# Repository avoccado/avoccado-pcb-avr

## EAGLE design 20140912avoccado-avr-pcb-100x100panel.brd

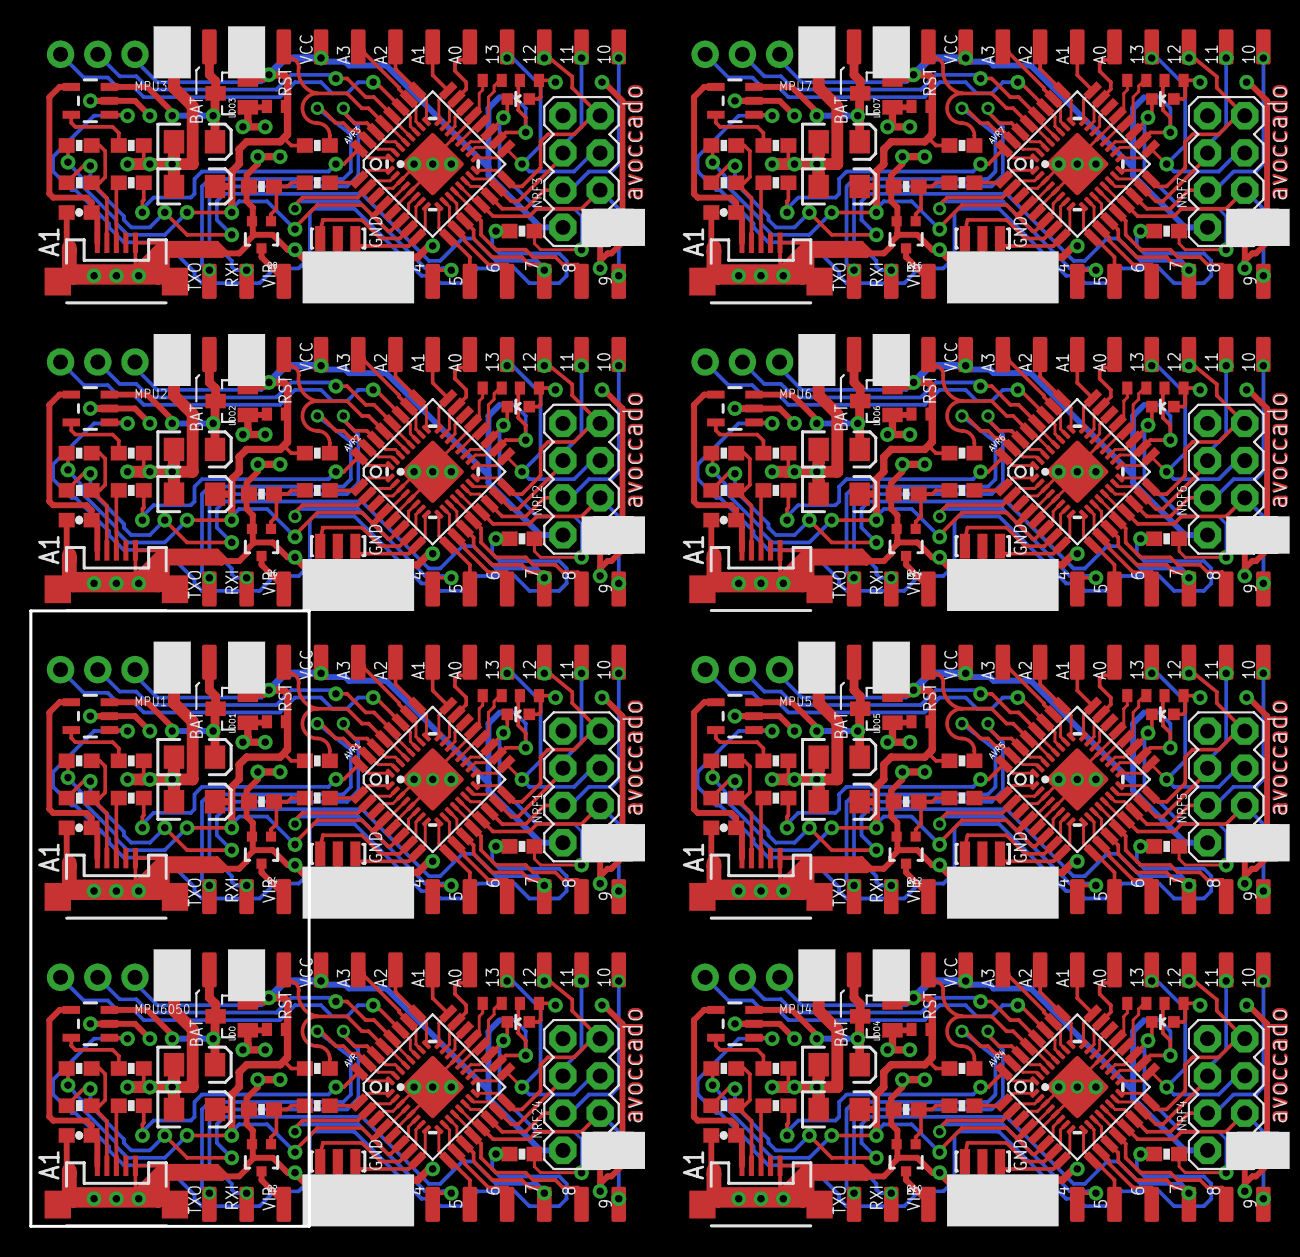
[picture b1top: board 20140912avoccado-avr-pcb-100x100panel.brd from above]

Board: 2 copper layers, 240 parts (0 on the bottom side), 288 nets.

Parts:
AVR, AVR1, AVR2, AVR3, AVR4, AVR5, AVR6, AVR7: ATMEGA328P; TQFP32-08
C1, C2, C3, C6, C7, C10, C11, C14, C15, C18, C21, C22, C25, C27, C28, C31, C33, C34, C37, C39, C40, C43, C45, C46: 0.1uF; C0402
C4, C9, C17, C24, C30, C36, C42, C48: 4.7uF; 0603-CAP
C5, C8, C12, C13, C16, C19, C20, C23, C26, C29, C32, C35, C38, C41, C44, C47: 10uF; EIA3216
D1, D2, D3, D4, D5, D6, D7, D8: LED; LED-0603
IC1, IC2, IC3, IC4, IC5, IC6, IC7, IC8: ATMEGA328P-20MU; MLF32
JP1, JP2, JP3, JP4, JP5, JP6, JP7, JP8, JP9, JP10, JP11, JP12, JP13, JP14, JP15, JP16, JP17, JP18, JP19, JP20, JP21, JP22, JP23, JP24, JP25, JP26, JP27, JP28, JP29, JP30, JP31, JP32, JP33, JP34, JP35, JP36, JP37, JP38, JP39, JP40, JP41, JP42, JP43, JP44, JP45, JP46, JP47, JP48: 1X04-SMD
LDO, LDO1, LDO2, LDO3, LDO4, LDO5, LDO6, LDO7: MCP1703CB; SOT23
MPU1, MPU2, MPU3, MPU4, MPU5, MPU6, MPU7, MPU6050: 1X04_NO_SILK
NRF1, NRF2, NRF3, NRF4, NRF5, NRF6, NRF7, NRF24: M04X2; 2X4
Q1, Q3, Q5, Q7, Q9, Q11, Q13, Q15: 16MHz; RESONATOR-SMD
Q2, Q4, Q6, Q8, Q10, Q12, Q14, Q16: FET; SOT323
R1, R10, R18, R26, R34, R42, R50, R58: 1K; 0603-RES
R2, R9, R17, R25, R33, R41, R49, R57: 10K; 0603-RES
R3, R4, R8, R11, R12, R16, R19, R20, R24, R27, R28, R32, R35, R36, R40, R43, R44, R48, R51, R52, R56, R59, R60, R64: 2K; 0603-RES
R5, R13, R21, R29, R37, R45, R53, R61: 1M; 0603-RES
R6, R7, R14, R15, R22, R23, R30, R31, R38, R39, R46, R47, R54, R55, R62, R63: 68; 0603-RES
U1, U2, U3, U4, U5, U6, U7, U8: MCP73831; SOT23-5
X1, X2, X3, X4, X5, X6, X7, X8: Micro USB; USB-MICROB

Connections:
3V1: AVR1.4, AVR1.6, AVR1.18, C2.1, C5.A, C6.2, IC1.4, IC1.6, IC1.18, JP1.4, LDO1.2, MPU1.2, NRF1.2, R9.2, R16.2
3V2: AVR2.4, AVR2.6, AVR2.18, C11.1, C12.A, C14.2, IC2.4, IC2.6, IC2.18, JP13.4, LDO2.2, MPU2.2, NRF2.2, R17.2, R24.2
3V3: AVR.4, AVR.6, AVR.18, C3.2, C10.1, C13.A, IC5.4, IC5.6, IC5.18, JP3.4, LDO.2, MPU6050.2, NRF24.2, R2.2, R8.2
3V4: AVR3.4, AVR3.6, AVR3.18, C18.1, C20.A, C21.2, IC3.4, IC3.6, IC3.18, JP19.4, LDO3.2, MPU3.2, NRF3.2, R25.2, R32.2
3V5: AVR4.4, AVR4.6, AVR4.18, C25.1, C26.A, C27.2, IC4.4, IC4.6, IC4.18, JP25.4, LDO4.2, MPU4.2, NRF4.2, R33.2, R40.2
3V6: AVR5.4, AVR5.6, AVR5.18, C31.1, C32.A, C33.2, IC6.4, IC6.6, IC6.18, JP31.4, LDO5.2, MPU5.2, NRF5.2, R41.2, R48.2
3V7: AVR6.4, AVR6.6, AVR6.18, C37.1, C38.A, C39.2, IC7.4, IC7.6, IC7.18, JP37.4, LDO6.2, MPU6.2, NRF6.2, R49.2, R56.2
3V8: AVR7.4, AVR7.6, AVR7.18, C43.1, C44.A, C45.2, IC8.4, IC8.6, IC8.18, JP43.4, LDO7.2, MPU7.2, NRF7.2, R57.2, R64.2
A0: AVR.23, IC5.23, JP5.4
A1: AVR.24, IC5.24, JP5.3
A2: AVR.25, IC5.25, JP5.2
A3: AVR.26, IC5.26, JP5.1
A4: AVR.27, IC5.27, MPU6050.4
A5: AVR.28, IC5.28, MPU6050.3
A6: AVR.19, D1.C, IC5.19, R4.1
A7: AVR.22, IC5.22
A8: AVR1.28, IC1.28, MPU1.3
A9: AVR1.27, IC1.27, MPU1.4
A10: AVR1.26, IC1.26, JP2.1
A11: AVR1.25, IC1.25, JP2.2
A12: AVR1.24, IC1.24, JP2.3
A13: AVR1.23, IC1.23, JP2.4
A14: AVR1.19, D2.C, IC1.19, R12.1
A15: AVR1.22, IC1.22
A16: AVR2.28, IC2.28, MPU2.3
A17: AVR2.27, IC2.27, MPU2.4
A18: AVR2.26, IC2.26, JP14.1
A19: AVR2.25, IC2.25, JP14.2
A20: AVR2.24, IC2.24, JP14.3
A21: AVR2.23, IC2.23, JP14.4
A22: AVR2.19, D3.C, IC2.19, R20.1
A23: AVR2.22, IC2.22
A24: AVR3.28, IC3.28, MPU3.3
A25: AVR3.27, IC3.27, MPU3.4
A26: AVR3.26, IC3.26, JP20.1
A27: AVR3.25, IC3.25, JP20.2
A28: AVR3.24, IC3.24, JP20.3
A29: AVR3.23, IC3.23, JP20.4
A30: AVR3.19, D4.C, IC3.19, R28.1
A31: AVR3.22, IC3.22
A32: AVR4.28, IC4.28, MPU4.3
A33: AVR4.27, IC4.27, MPU4.4
A34: AVR4.26, IC4.26, JP26.1
A35: AVR4.25, IC4.25, JP26.2
A36: AVR4.24, IC4.24, JP26.3
A37: AVR4.23, IC4.23, JP26.4
A38: AVR4.19, D5.C, IC4.19, R36.1
A39: AVR4.22, IC4.22
A40: AVR5.28, IC6.28, MPU5.3
A41: AVR5.27, IC6.27, MPU5.4
A42: AVR5.26, IC6.26, JP32.1
A43: AVR5.25, IC6.25, JP32.2
A44: AVR5.24, IC6.24, JP32.3
A45: AVR5.23, IC6.23, JP32.4
A46: AVR5.19, D6.C, IC6.19, R44.1
A47: AVR5.22, IC6.22
A48: AVR6.28, IC7.28, MPU6.3
A49: AVR6.27, IC7.27, MPU6.4
A50: AVR6.26, IC7.26, JP38.1
A51: AVR6.25, IC7.25, JP38.2
A52: AVR6.24, IC7.24, JP38.3
A53: AVR6.23, IC7.23, JP38.4
A54: AVR6.19, D7.C, IC7.19, R52.1
A55: AVR6.22, IC7.22
A56: AVR7.28, IC8.28, MPU7.3
A57: AVR7.27, IC8.27, MPU7.4
A58: AVR7.26, IC8.26, JP44.1
A59: AVR7.25, IC8.25, JP44.2
A60: AVR7.24, IC8.24, JP44.3
A61: AVR7.23, IC8.23, JP44.4
A62: AVR7.19, D8.C, IC8.19, R60.1
A63: AVR7.22, IC8.22
AREF: AVR.20, C1.2, IC5.20
AREF1: AVR1.20, C7.2, IC1.20
AREF2: AVR2.20, C15.2, IC2.20
AREF3: AVR3.20, C22.2, IC3.20
AREF4: AVR4.20, C28.2, IC4.20
AREF5: AVR5.20, C34.2, IC6.20
AREF6: AVR6.20, C40.2, IC7.20
AREF7: AVR7.20, C46.2, IC8.20
BUS: C4.1, U2.4, X1.VBUS
BUS1: C9.1, U1.4, X2.VBUS
BUS2: C17.1, U3.4, X3.VBUS
BUS3: C24.1, U4.4, X4.VBUS
BUS4: C30.1, U5.4, X5.VBUS
BUS5: C36.1, U6.4, X6.VBUS
BUS6: C42.1, U7.4, X7.VBUS
BUS7: C48.1, U8.4, X8.VBUS
D1: AVR1.13, IC1.13, JP6.1, NRF1.3
D2: AVR.32, IC5.32, R7.2
D3: AVR.1, IC5.1, R1.1
D4: AVR.2, IC5.2, JP10.2
D5: AVR.9, IC5.9, JP10.1
D6: AVR.10, IC5.10, JP9.4
D7: AVR.11, IC5.11, JP9.3, R6.2
D8: AVR.12, IC5.12, JP9.2
D9: AVR.13, IC5.13, JP9.1, NRF24.3
D10: AVR.14, IC5.14, JP8.4, NRF24.4
D11: AVR1.12, IC1.12, JP6.2
D12: AVR1.32, IC1.32, R15.2
D13: AVR1.1, IC1.1, R10.1
D14: AVR1.2, IC1.2, JP7.2
D15: AVR1.9, IC1.9, JP7.1
D16: AVR1.10, IC1.10, JP6.4
D17: AVR1.11, IC1.11, JP6.3, R14.2
D18: AVR1.14, IC1.14, JP4.4, NRF1.4
D19: AVR2.13, IC2.13, JP16.1, NRF2.3
D20: AVR2.12, IC2.12, JP16.2
D21: AVR2.32, IC2.32, R23.2
D22: AVR2.1, IC2.1, R18.1
D23: AVR2.2, IC2.2, JP17.2
D24: AVR2.9, IC2.9, JP17.1
D25: AVR2.10, IC2.10, JP16.4
D26: AVR2.11, IC2.11, JP16.3, R22.2
D27: AVR2.14, IC2.14, JP15.4, NRF2.4
D28: AVR3.13, IC3.13, JP22.1, NRF3.3
D29: AVR3.12, IC3.12, JP22.2
D30: AVR3.32, IC3.32, R31.2
D31: AVR3.1, IC3.1, R26.1
D32: AVR3.2, IC3.2, JP23.2
D33: AVR3.9, IC3.9, JP23.1
D34: AVR3.10, IC3.10, JP22.4
D35: AVR3.11, IC3.11, JP22.3, R30.2
D36: AVR3.14, IC3.14, JP21.4, NRF3.4
D37: AVR4.13, IC4.13, JP28.1, NRF4.3
D38: AVR4.12, IC4.12, JP28.2
D39: AVR4.32, IC4.32, R39.2
D40: AVR4.1, IC4.1, R34.1
D41: AVR4.2, IC4.2, JP29.2
D42: AVR4.9, IC4.9, JP29.1
D43: AVR4.10, IC4.10, JP28.4
D44: AVR4.11, IC4.11, JP28.3, R38.2
D45: AVR4.14, IC4.14, JP27.4, NRF4.4
D46: AVR5.13, IC6.13, JP34.1, NRF5.3
D47: AVR5.12, IC6.12, JP34.2
D48: AVR5.32, IC6.32, R47.2
D49: AVR5.1, IC6.1, R42.1
D50: AVR5.2, IC6.2, JP35.2
D51: AVR5.9, IC6.9, JP35.1
D52: AVR5.10, IC6.10, JP34.4
D53: AVR5.11, IC6.11, JP34.3, R46.2
D54: AVR5.14, IC6.14, JP33.4, NRF5.4
D55: AVR6.13, IC7.13, JP40.1, NRF6.3
D56: AVR6.12, IC7.12, JP40.2
D57: AVR6.32, IC7.32, R55.2
D58: AVR6.1, IC7.1, R50.1
D59: AVR6.2, IC7.2, JP41.2
D60: AVR6.9, IC7.9, JP41.1
D61: AVR6.10, IC7.10, JP40.4
D62: AVR6.11, IC7.11, JP40.3, R54.2
D63: AVR6.14, IC7.14, JP39.4, NRF6.4
D64: AVR7.13, IC8.13, JP46.1, NRF7.3
D65: AVR7.12, IC8.12, JP46.2
D66: AVR7.32, IC8.32, R63.2
D67: AVR7.1, IC8.1, R58.1
D68: AVR7.2, IC8.2, JP47.2
D69: AVR7.9, IC8.9, JP47.1
D70: AVR7.10, IC8.10, JP46.4
D71: AVR7.11, IC8.11, JP46.3, R62.2
D72: AVR7.14, IC8.14, JP45.4, NRF7.4
GND: AVR.3, AVR.5, AVR.21, C1.1, C3.1, C4.2, C10.2, C13.C, C19.C, D1.A, IC5.3, IC5.5, IC5.21, JP3.2, JP10.3, JP10.4, JP11.1, LDO.1, MPU6050.1, NRF24.1, Q1.2, Q2.2, R3.1, R5.1, U2.2, X1.GND
GND1: AVR1.3, AVR1.5, AVR1.21, C2.2, C5.C, C6.1, C7.1, C8.C, C9.2, D2.A, IC1.3, IC1.5, IC1.21, JP1.2, JP7.3, JP7.4, JP12.1, LDO1.1, MPU1.1, NRF1.1, Q3.2, Q4.2, R11.1, R13.1, U1.2, X2.GND
GND2: AVR2.3, AVR2.5, AVR2.21, C11.2, C12.C, C14.1, C15.1, C16.C, C17.2, D3.A, IC2.3, IC2.5, IC2.21, JP13.2, JP17.3, JP17.4, JP18.1, LDO2.1, MPU2.1, NRF2.1, Q5.2, Q6.2, R19.1, R21.1, U3.2, X3.GND
GND3: AVR3.3, AVR3.5, AVR3.21, C18.2, C20.C, C21.1, C22.1, C23.C, C24.2, D4.A, IC3.3, IC3.5, IC3.21, JP19.2, JP23.3, JP23.4, JP24.1, LDO3.1, MPU3.1, NRF3.1, Q7.2, Q8.2, R27.1, R29.1, U4.2, X4.GND
GND4: AVR4.3, AVR4.5, AVR4.21, C25.2, C26.C, C27.1, C28.1, C29.C, C30.2, D5.A, IC4.3, IC4.5, IC4.21, JP25.2, JP29.3, JP29.4, JP30.1, LDO4.1, MPU4.1, NRF4.1, Q9.2, Q10.2, R35.1, R37.1, U5.2, X5.GND
GND5: AVR5.3, AVR5.5, AVR5.21, C31.2, C32.C, C33.1, C34.1, C35.C, C36.2, D6.A, IC6.3, IC6.5, IC6.21, JP31.2, JP35.3, JP35.4, JP36.1, LDO5.1, MPU5.1, NRF5.1, Q11.2, Q12.2, R43.1, R45.1, U6.2, X6.GND
GND6: AVR6.3, AVR6.5, AVR6.21, C37.2, C38.C, C39.1, C40.1, C41.C, C42.2, D7.A, IC7.3, IC7.5, IC7.21, JP37.2, JP41.3, JP41.4, JP42.1, LDO6.1, MPU6.1, NRF6.1, Q13.2, Q14.2, R51.1, R53.1, U7.2, X7.GND
GND7: AVR7.3, AVR7.5, AVR7.21, C43.2, C44.C, C45.1, C46.1, C47.C, C48.2, D8.A, IC8.3, IC8.5, IC8.21, JP43.2, JP47.3, JP47.4, JP48.1, LDO7.1, MPU7.1, NRF7.1, Q15.2, Q16.2, R59.1, R61.1, U8.2, X8.GND
MISO: AVR.16, IC5.16, JP8.2, NRF24.7
MISO1: AVR1.16, IC1.16, JP4.2, NRF1.7
MISO2: AVR2.16, IC2.16, JP15.2, NRF2.7
MISO3: AVR3.16, IC3.16, JP21.2, NRF3.7
MISO4: AVR4.16, IC4.16, JP27.2, NRF4.7
MISO5: AVR5.16, IC6.16, JP33.2, NRF5.7
MISO6: AVR6.16, IC7.16, JP39.2, NRF6.7
MISO7: AVR7.16, IC8.16, JP45.2, NRF7.7
MOSI: AVR.15, IC5.15, JP8.3, NRF24.6
MOSI1: AVR1.15, IC1.15, JP4.3, NRF1.6
MOSI2: AVR2.15, IC2.15, JP15.3, NRF2.6
MOSI3: AVR3.15, IC3.15, JP21.3, NRF3.6
MOSI4: AVR4.15, IC4.15, JP27.3, NRF4.6
MOSI5: AVR5.15, IC6.15, JP33.3, NRF5.6
MOSI6: AVR6.15, IC7.15, JP39.3, NRF6.6
MOSI7: AVR7.15, IC8.15, JP45.3, NRF7.6
unnamed: AVR.8, IC5.8, Q1.1
unnamed: AVR.7, IC5.7, Q1.3
unnamed: R3.2, U2.5
unnamed: R4.2, U2.1
unnamed: AVR1.8, IC1.8, Q3.1
unnamed: Q2.1, R1.2, R5.2
unnamed: AVR1.7, IC1.7, Q3.3
unnamed: R11.2, U1.5
unnamed: R12.2, U1.1
unnamed: Q4.1, R10.2, R13.2
unnamed: AVR2.8, IC2.8, Q5.1
unnamed: AVR2.7, IC2.7, Q5.3
unnamed: R19.2, U3.5
unnamed: R20.2, U3.1
unnamed: Q6.1, R18.2, R21.2
unnamed: AVR3.8, IC3.8, Q7.1
unnamed: AVR3.7, IC3.7, Q7.3
unnamed: R27.2, U4.5
unnamed: R28.2, U4.1
unnamed: Q8.1, R26.2, R29.2
unnamed: AVR4.8, IC4.8, Q9.1
unnamed: AVR4.7, IC4.7, Q9.3
unnamed: R35.2, U5.5
unnamed: R36.2, U5.1
unnamed: Q10.1, R34.2, R37.2
unnamed: AVR5.8, IC6.8, Q11.1
unnamed: AVR5.7, IC6.7, Q11.3
unnamed: R43.2, U6.5
unnamed: R44.2, U6.1
unnamed: Q12.1, R42.2, R45.2
unnamed: AVR6.8, IC7.8, Q13.1
unnamed: AVR6.7, IC7.7, Q13.3
unnamed: R51.2, U7.5
unnamed: R52.2, U7.1
unnamed: Q14.1, R50.2, R53.2
unnamed: AVR7.8, IC8.8, Q15.1
unnamed: AVR7.7, IC8.7, Q15.3
unnamed: R59.2, U8.5
unnamed: R60.2, U8.1
unnamed: Q16.1, R58.2, R61.2
RESET: AVR.29, IC5.29, JP3.3, R2.1
RESET1: AVR1.29, IC1.29, JP1.3, R9.1
RESET2: AVR2.29, IC2.29, JP13.3, R17.1
RESET3: AVR3.29, IC3.29, JP19.3, R25.1
RESET4: AVR4.29, IC4.29, JP25.3, R33.1
RESET5: AVR5.29, IC6.29, JP31.3, R41.1
RESET6: AVR6.29, IC7.29, JP37.3, R49.1
RESET7: AVR7.29, IC8.29, JP43.3, R57.1
RXI: AVR.30, IC5.30, JP11.3
RXI1: AVR1.30, IC1.30, JP12.3
RXI2: AVR2.30, IC2.30, JP18.3
RXI3: AVR3.30, IC3.30, JP24.3
RXI4: AVR4.30, IC4.30, JP30.3
RXI5: AVR5.30, IC6.30, JP36.3
RXI6: AVR6.30, IC7.30, JP42.3
RXI7: AVR7.30, IC8.30, JP48.3
SCK: AVR.17, IC5.17, JP8.1, NRF24.5
SCK1: AVR1.17, IC1.17, JP4.1, NRF1.5
SCK2: AVR2.17, IC2.17, JP15.1, NRF2.5
SCK3: AVR3.17, IC3.17, JP21.1, NRF3.5
SCK4: AVR4.17, IC4.17, JP27.1, NRF4.5
SCK5: AVR5.17, IC6.17, JP33.1, NRF5.5
SCK6: AVR6.17, IC7.17, JP39.1, NRF6.5
SCK7: AVR7.17, IC8.17, JP45.1, NRF7.5
TXO: AVR.31, IC5.31, JP11.4
TXO1: AVR1.31, IC1.31, JP12.4
TXO2: AVR2.31, IC2.31, JP18.4
TXO3: AVR3.31, IC3.31, JP24.4
TXO4: AVR4.31, IC4.31, JP30.4
TXO5: AVR5.31, IC6.31, JP36.4
TXO6: AVR6.31, IC7.31, JP42.4
TXO7: AVR7.31, IC8.31, JP48.4
USB-D+: R7.1, X1.D+
USB-D+1: R15.1, X2.D+
USB-D+2: R23.1, X3.D+
USB-D+3: R31.1, X4.D+
USB-D+4: R39.1, X5.D+
USB-D+5: R47.1, X6.D+
USB-D+6: R55.1, X7.D+
USB-D+7: R63.1, X8.D+
USB-D-: R6.1, R8.1, X1.D-
USB-D-1: R14.1, R16.1, X2.D-
USB-D-2: R22.1, R24.1, X3.D-
USB-D-3: R30.1, R32.1, X4.D-
USB-D-4: R38.1, R40.1, X5.D-
USB-D-5: R46.1, R48.1, X6.D-
USB-D-6: R54.1, R56.1, X7.D-
USB-D-7: R62.1, R64.1, X8.D-
VBAT: C19.A, JP3.1, LDO.3, U2.3
VBAT1: C8.A, JP1.1, LDO1.3, U1.3
VBAT2: C16.A, JP13.1, LDO2.3, U3.3
VBAT3: C23.A, JP19.1, LDO3.3, U4.3
VBAT4: C29.A, JP25.1, LDO4.3, U5.3
VBAT5: C35.A, JP31.1, LDO5.3, U6.3
VBAT6: C41.A, JP37.1, LDO6.3, U7.3
VBAT7: C47.A, JP43.1, LDO7.3, U8.3
VIBR: JP11.2, Q2.3
VIBR1: JP12.2, Q4.3
VIBR2: JP18.2, Q6.3
VIBR3: JP24.2, Q8.3
VIBR4: JP30.2, Q10.3
VIBR5: JP36.2, Q12.3
VIBR6: JP42.2, Q14.3
VIBR7: JP48.2, Q16.3

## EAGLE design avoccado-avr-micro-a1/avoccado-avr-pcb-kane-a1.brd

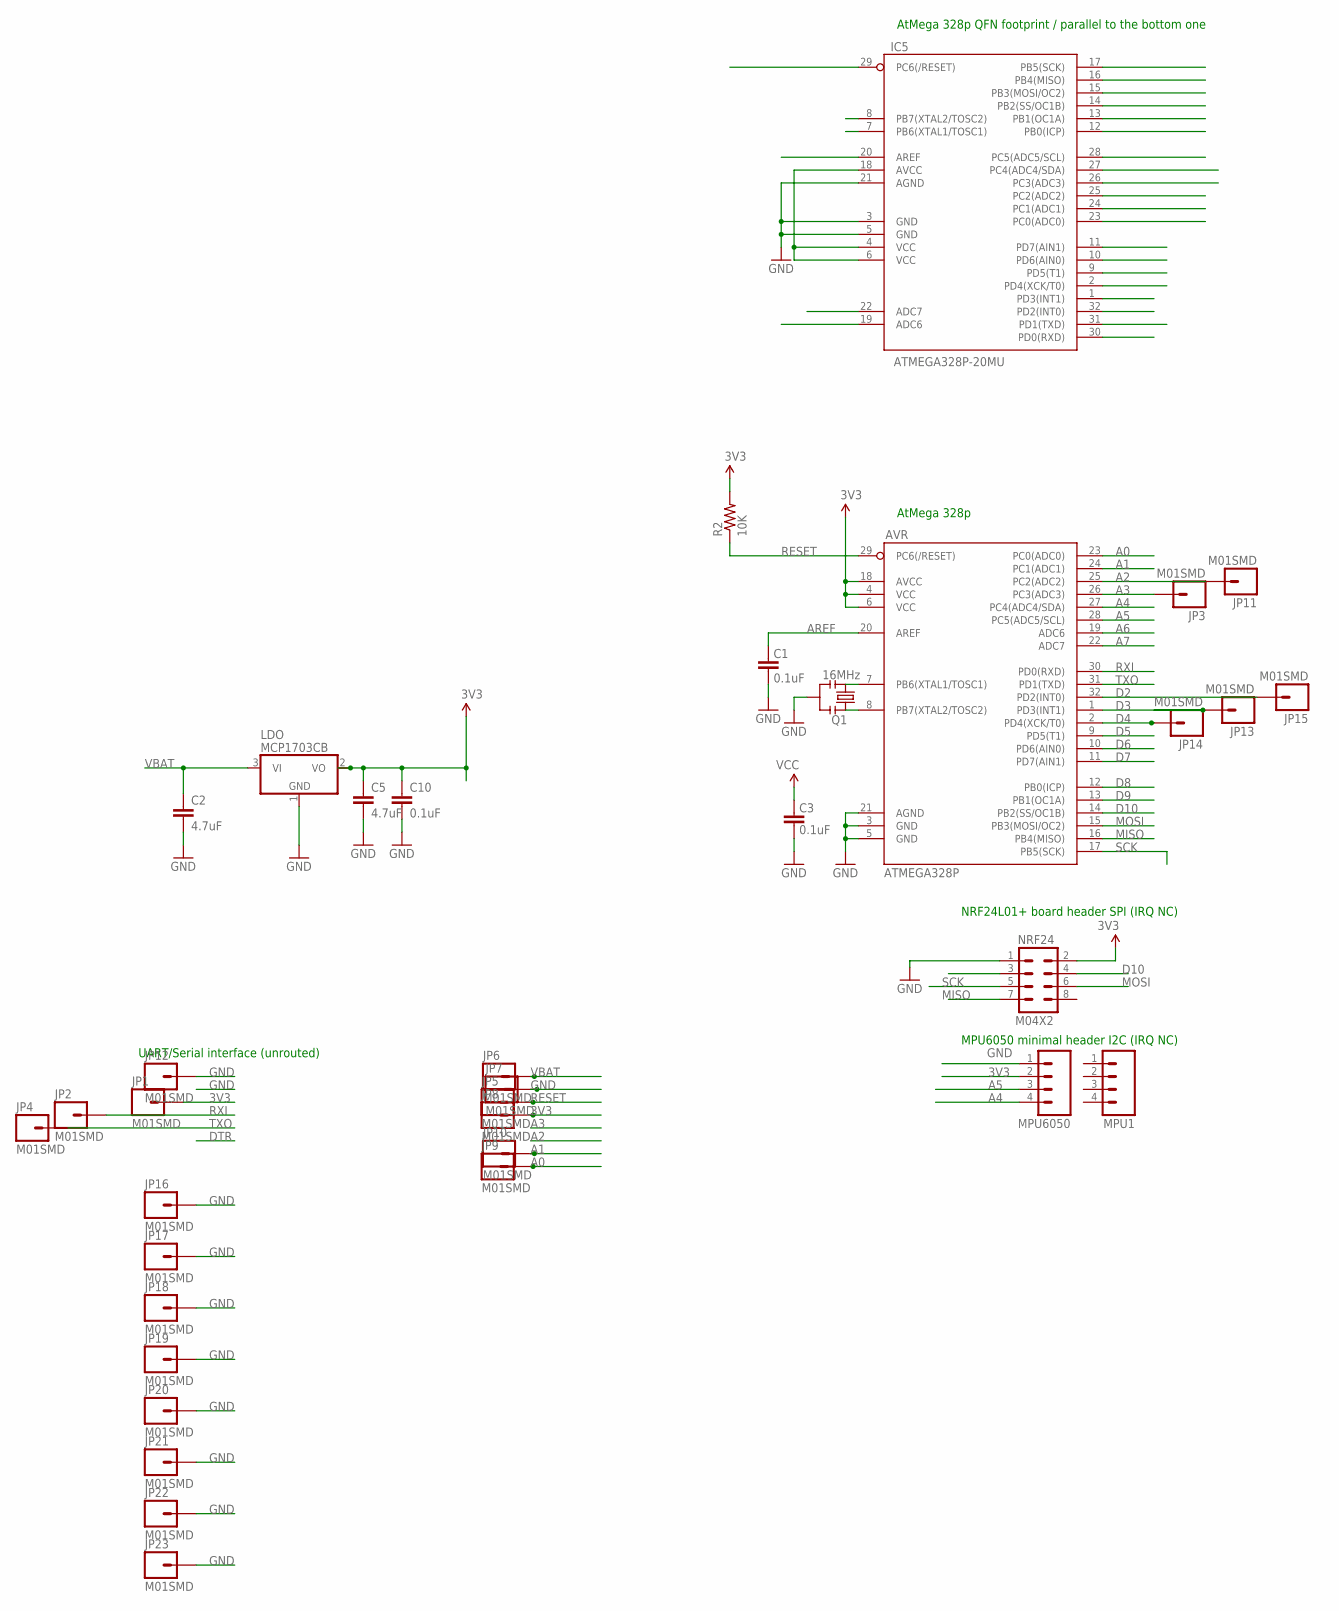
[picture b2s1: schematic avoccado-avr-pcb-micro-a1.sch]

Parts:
AVR: ATMEGA328P; TQFP32-08
C1, C3, C10: 0.1uF; C0402
C2, C5: 4.7uF; 0603-CAP
IC5: ATMEGA328P-20MU; MLF32
JP1, JP2, JP3, JP4, JP5, JP6, JP7, JP8, JP9, JP10, JP11, JP12, JP13, JP14, JP15, JP16, JP17, JP18, JP19, JP20, JP21, JP22, JP23: M01SMD; LUXEON-PAD
LDO: MCP1703CB; SOT23
MPU1, MPU6050: M041X04_NO_SILK; 1X04_NO_SILK
NRF24: M04X2; 2X4
Q1: 16MHz; RESONATOR-SMD
R2: 10K; 0603-RES

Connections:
3V3: AVR.4 (VCC), AVR.6 (VCC), AVR.18 (AVCC), C3.2, C5.1, C10.1, IC5.4 (VCC), IC5.6 (VCC), IC5.18 (AVCC), JP1.P$1, JP8.P$1, LDO.2 (VO), MPU6050.2, NRF24.2, R2.2; also elsewhere on the board
A0: AVR.23 (PC0(ADC0)), IC5.23 (PC0(ADC0)), JP9.P$1
A1: AVR.24 (PC1(ADC1)), IC5.24 (PC1(ADC1)), JP10.P$1
A2: AVR.25 (PC2(ADC2)), IC5.25 (PC2(ADC2)), JP11.P$1
A3: AVR.26 (PC3(ADC3)), IC5.26 (PC3(ADC3)), JP3.P$1
A4: AVR.27 (PC4(ADC4/SDA)), IC5.27 (PC4(ADC4/SDA)), MPU6050.4
A5: AVR.28 (PC5(ADC5/SCL)), IC5.28 (PC5(ADC5/SCL)), MPU6050.3
A6: AVR.19 (ADC6), IC5.19 (ADC6)
A7: AVR.22 (ADC7), IC5.22 (ADC7)
AREF: AVR.20 (AREF), C1.2, IC5.20 (AREF)
D2: AVR.32 (PD2(INT0)), IC5.32 (PD2(INT0)), JP15.P$1
D3: AVR.1 (PD3(INT1)), IC5.1 (PD3(INT1)), JP13.P$1
D4: AVR.2 (PD4(XCK/T0)), IC5.2 (PD4(XCK/T0)), JP14.P$1
D5: AVR.9 (PD5(T1)), IC5.9 (PD5(T1))
D6: AVR.10 (PD6(AIN0)), IC5.10 (PD6(AIN0))
D7: AVR.11 (PD7(AIN1)), IC5.11 (PD7(AIN1))
D8: AVR.12 (PB0(ICP)), IC5.12 (PB0(ICP))
D9: AVR.13 (PB1(OC1A)), IC5.13 (PB1(OC1A)), NRF24.3
D10: AVR.14 (PB2(SS/OC1B)), IC5.14 (PB2(SS/OC1B)), NRF24.4
GND: AVR.3 (GND), AVR.5 (GND), AVR.21 (AGND), C1.1, C2.2, C3.1, C5.2, C10.2, IC5.3 (GND), IC5.5 (GND), IC5.21 (AGND), JP7.P$1, JP12.P$1, JP16.P$1, JP17.P$1, JP18.P$1, JP19.P$1, JP20.P$1, JP21.P$1, JP22.P$1, JP23.P$1, LDO.1 (GND), MPU6050.1, NRF24.1, Q1.2; also elsewhere on the board
MISO: AVR.16 (PB4(MISO)), IC5.16 (PB4(MISO)), NRF24.7
MOSI: AVR.15 (PB3(MOSI/OC2)), IC5.15 (PB3(MOSI/OC2)), NRF24.6
unnamed: AVR.8 (PB7(XTAL2/TOSC2)), IC5.8 (PB7(XTAL2/TOSC2)), Q1.1
unnamed: AVR.7 (PB6(XTAL1/TOSC1)), IC5.7 (PB6(XTAL1/TOSC1)), Q1.3
RESET: AVR.29 (PC6(/RESET)), IC5.29 (PC6(/RESET)), JP5.P$1, R2.1; also elsewhere on the board
RXI: AVR.30 (PD0(RXD)), IC5.30 (PD0(RXD)), JP2.P$1
SCK: AVR.17 (PB5(SCK)), IC5.17 (PB5(SCK)), NRF24.5
TXO: AVR.31 (PD1(TXD)), IC5.31 (PD1(TXD)), JP4.P$1
VBAT: C2.1, JP6.P$1, LDO.3 (VI); also elsewhere on the board

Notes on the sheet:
NRF24L01+ board header SPI (IRQ NC)
MPU6050 minimal header I2C (IRQ NC)
AtMega 328p
AtMega 328p QFN footprint / parallel to the bottom one
UART/Serial interface (unrouted)

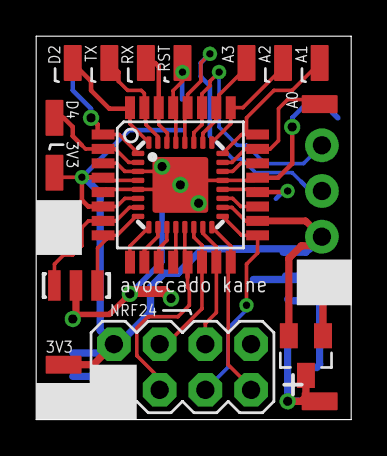
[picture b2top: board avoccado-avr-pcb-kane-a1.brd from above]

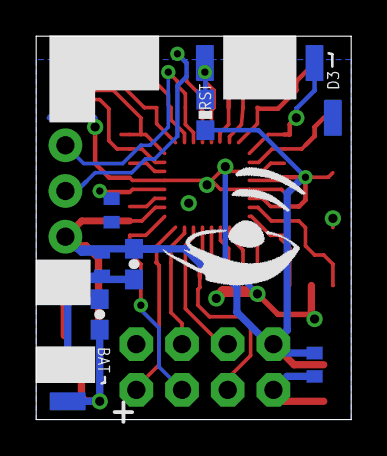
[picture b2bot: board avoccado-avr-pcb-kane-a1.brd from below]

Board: 2 copper layers, 17.5 x 21.3 mm, 37 parts (17 on the bottom side), 29 nets.

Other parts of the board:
JP24, JP25: M01SMD; LUXEON-PAD
LDO1: MCP1703CB; SOT23

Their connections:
3V3: LDO1.2; also elsewhere on the board
GND: LDO1.1; also elsewhere on the board
RESET: JP25.P$1; also elsewhere on the board
VBAT: JP24.P$1, LDO1.3; also elsewhere on the board

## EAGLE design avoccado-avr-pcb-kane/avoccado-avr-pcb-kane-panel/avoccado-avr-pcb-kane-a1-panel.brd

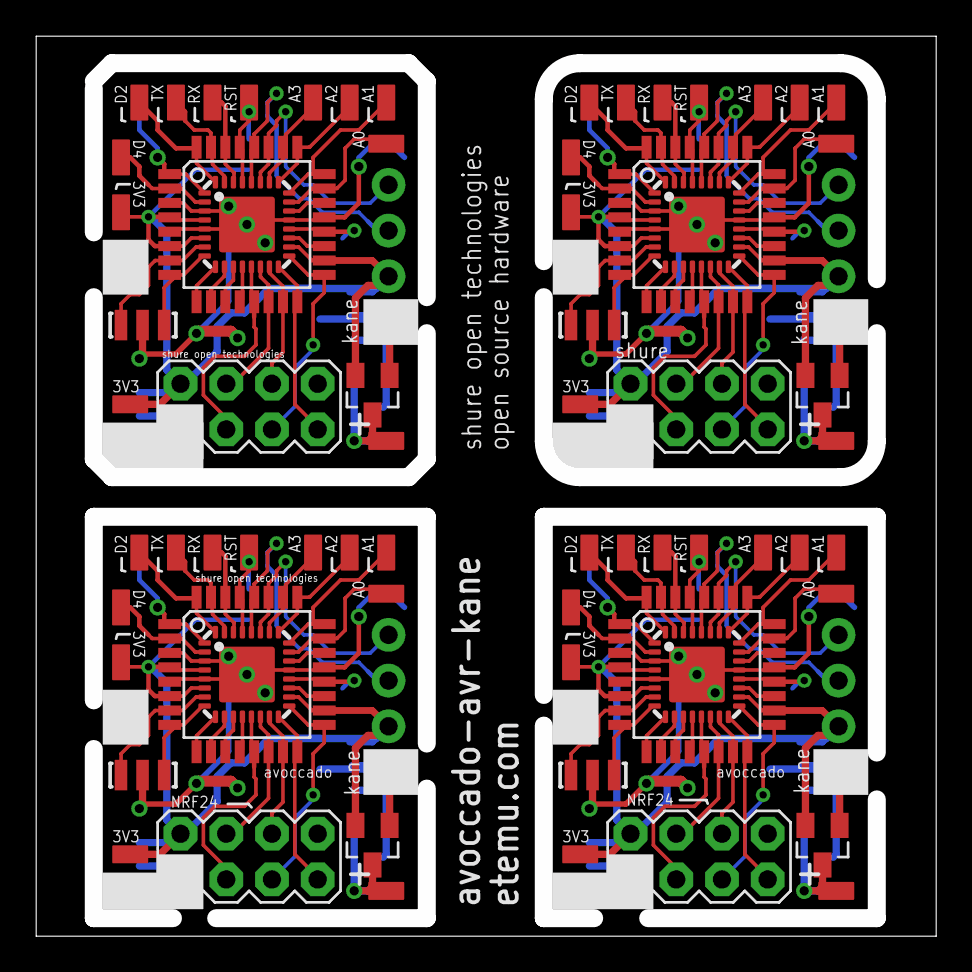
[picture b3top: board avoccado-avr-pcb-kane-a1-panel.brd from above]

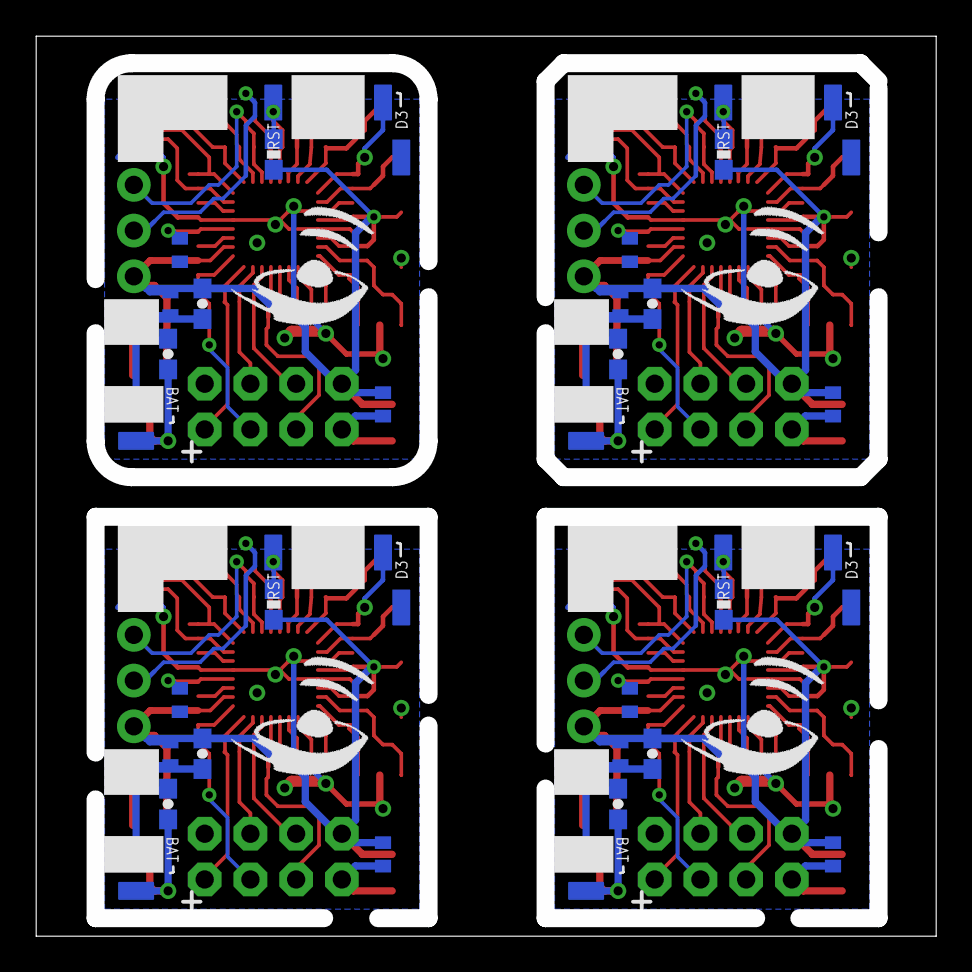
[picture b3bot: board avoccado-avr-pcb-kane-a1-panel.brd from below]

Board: 2 copper layers, 50.0 x 50.0 mm, 148 parts (68 on the bottom side), 116 nets.

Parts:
AVR, AVR1, AVR2, AVR3: ATMEGA328P; TQFP32-08
C1, C3, C4, C6, C7, C10, C11, C12, C13, C16, C17, C18: 0.1uF; C0402
C2, C5, C8, C9, C14, C15, C19, C20: 4.7uF; 0603-CAP
IC1, IC2, IC3, IC5: ATMEGA328P-20MU; MLF32
JP1, JP2, JP3, JP4, JP5, JP6, JP7, JP8, JP9, JP10, JP11, JP12, JP13, JP14, JP15, JP16, JP17, JP18, JP19, JP20, JP21, JP22, JP23, JP24, JP25, JP26, JP27, JP28, JP29, JP30, JP31, JP32, JP33, JP34, JP35, JP36, JP37, JP38, JP39, JP40, JP41, JP42, JP43, JP44, JP45, JP46, JP47, JP48, JP49, JP50, JP51, JP52, JP53, JP54, JP55, JP56, JP57, JP58, JP59, JP60, JP61, JP62, JP63, JP64, JP65, JP66, JP67, JP68, JP69, JP70, JP71, JP72, JP73, JP74, JP75, JP76, JP77, JP78, JP79, JP80, JP81, JP82, JP83, JP84, JP85, JP86, JP87, JP88, JP89, JP90, JP91, JP92, JP93, JP94, JP95, JP96, JP97, JP98, JP99, JP100: M01SMD; LUXEON-PAD
LDO1, LDO2, LDO3, LDO4: MCP1703CB; SOT23
MPU1, MPU2, MPU3, MPU6050: 1X04_NO_SILK
NRF1, NRF2, NRF3, NRF24: M04X2; 2X4
Q1, Q2, Q3, Q4: 16MHz; RESONATOR-SMD
R1, R2, R3, R4: 10K; 0603-RES

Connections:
3V1: AVR1.4, AVR1.6, AVR1.18, C4.1, C6.2, C9.1, IC1.4, IC1.6, IC1.18, JP26.P$1, JP32.P$1, LDO2.2, MPU1.2, NRF1.2, R1.2
3V2: AVR2.4, AVR2.6, AVR2.18, C11.1, C12.2, C15.1, IC2.4, IC2.6, IC2.18, JP51.P$1, JP57.P$1, LDO3.2, MPU2.2, NRF2.2, R3.2
3V3: AVR.4, AVR.6, AVR.18, C3.2, C5.1, C10.1, IC5.4, IC5.6, IC5.18, JP1.P$1, JP8.P$1, LDO1.2, MPU6050.2, NRF24.2, R2.2
3V4: AVR3.4, AVR3.6, AVR3.18, C16.1, C17.2, C20.1, IC3.4, IC3.6, IC3.18, JP76.P$1, JP82.P$1, LDO4.2, MPU3.2, NRF3.2, R4.2
A0: AVR.23, IC5.23, JP9.P$1
A1: AVR.24, IC5.24, JP10.P$1
A2: AVR.25, IC5.25, JP11.P$1
A3: AVR.26, IC5.26, JP3.P$1
A4: AVR.27, IC5.27, MPU6050.4
A5: AVR.28, IC5.28, MPU6050.3
A6: AVR.19, IC5.19
A7: AVR.22, IC5.22
A8: AVR1.28, IC1.28, MPU1.3
A9: AVR1.27, IC1.27, MPU1.4
A10: AVR1.26, IC1.26, JP35.P$1
A11: AVR1.25, IC1.25, JP36.P$1
A12: AVR1.24, IC1.24, JP34.P$1
A13: AVR1.23, IC1.23, JP33.P$1
A14: AVR1.19, IC1.19
A15: AVR1.22, IC1.22
A16: AVR2.28, IC2.28, MPU2.3
A17: AVR2.27, IC2.27, MPU2.4
A18: AVR2.26, IC2.26, JP60.P$1
A19: AVR2.25, IC2.25, JP61.P$1
A20: AVR2.24, IC2.24, JP59.P$1
A21: AVR2.23, IC2.23, JP58.P$1
A22: AVR2.19, IC2.19
A23: AVR2.22, IC2.22
A24: AVR3.28, IC3.28, MPU3.3
A25: AVR3.27, IC3.27, MPU3.4
A26: AVR3.26, IC3.26, JP85.P$1
A27: AVR3.25, IC3.25, JP86.P$1
A28: AVR3.24, IC3.24, JP84.P$1
A29: AVR3.23, IC3.23, JP83.P$1
A30: AVR3.19, IC3.19
A31: AVR3.22, IC3.22
AREF: AVR.20, C1.2, IC5.20
AREF1: AVR1.20, C7.2, IC1.20
AREF2: AVR2.20, C13.2, IC2.20
AREF3: AVR3.20, C18.2, IC3.20
D1: AVR1.13, IC1.13, NRF1.3
D2: AVR.32, IC5.32, JP15.P$1
D3: AVR.1, IC5.1, JP13.P$1
D4: AVR.2, IC5.2, JP14.P$1
D5: AVR.9, IC5.9
D6: AVR.10, IC5.10
D7: AVR.11, IC5.11
D8: AVR.12, IC5.12
D9: AVR.13, IC5.13, NRF24.3
D10: AVR.14, IC5.14, NRF24.4
D11: AVR1.12, IC1.12
D12: AVR1.32, IC1.32, JP40.P$1
D13: AVR1.1, IC1.1, JP38.P$1
D14: AVR1.2, IC1.2, JP39.P$1
D15: AVR1.9, IC1.9
D16: AVR1.10, IC1.10
D17: AVR1.11, IC1.11
D18: AVR1.14, IC1.14, NRF1.4
D19: AVR2.13, IC2.13, NRF2.3
D20: AVR2.12, IC2.12
D21: AVR2.32, IC2.32, JP65.P$1
D22: AVR2.1, IC2.1, JP63.P$1
D23: AVR2.2, IC2.2, JP64.P$1
D24: AVR2.9, IC2.9
D25: AVR2.10, IC2.10
D26: AVR2.11, IC2.11
D27: AVR2.14, IC2.14, NRF2.4
D28: AVR3.13, IC3.13, NRF3.3
D29: AVR3.12, IC3.12
D30: AVR3.32, IC3.32, JP90.P$1
D31: AVR3.1, IC3.1, JP88.P$1
D32: AVR3.2, IC3.2, JP89.P$1
D33: AVR3.9, IC3.9
D34: AVR3.10, IC3.10
D35: AVR3.11, IC3.11
D36: AVR3.14, IC3.14, NRF3.4
GND: AVR.3, AVR.5, AVR.21, C1.1, C2.2, C3.1, C5.2, C10.2, IC5.3, IC5.5, IC5.21, JP7.P$1, JP12.P$1, JP16.P$1, JP17.P$1, JP18.P$1, JP19.P$1, JP20.P$1, JP21.P$1, JP22.P$1, JP23.P$1, LDO1.1, MPU6050.1, NRF24.1, Q1.2
GND1: AVR1.3, AVR1.5, AVR1.21, C4.2, C6.1, C7.1, C8.2, C9.2, IC1.3, IC1.5, IC1.21, JP31.P$1, JP37.P$1, JP41.P$1, JP42.P$1, JP43.P$1, JP44.P$1, JP45.P$1, JP46.P$1, JP47.P$1, JP48.P$1, LDO2.1, MPU1.1, NRF1.1, Q2.2
GND2: AVR2.3, AVR2.5, AVR2.21, C11.2, C12.1, C13.1, C14.2, C15.2, IC2.3, IC2.5, IC2.21, JP56.P$1, JP62.P$1, JP66.P$1, JP67.P$1, JP68.P$1, JP69.P$1, JP70.P$1, JP71.P$1, JP72.P$1, JP73.P$1, LDO3.1, MPU2.1, NRF2.1, Q3.2
GND3: AVR3.3, AVR3.5, AVR3.21, C16.2, C17.1, C18.1, C19.2, C20.2, IC3.3, IC3.5, IC3.21, JP81.P$1, JP87.P$1, JP91.P$1, JP92.P$1, JP93.P$1, JP94.P$1, JP95.P$1, JP96.P$1, JP97.P$1, JP98.P$1, LDO4.1, MPU3.1, NRF3.1, Q4.2
MISO: AVR.16, IC5.16, NRF24.7
MISO1: AVR1.16, IC1.16, NRF1.7
MISO2: AVR2.16, IC2.16, NRF2.7
MISO3: AVR3.16, IC3.16, NRF3.7
MOSI: AVR.15, IC5.15, NRF24.6
MOSI1: AVR1.15, IC1.15, NRF1.6
MOSI2: AVR2.15, IC2.15, NRF2.6
MOSI3: AVR3.15, IC3.15, NRF3.6
unnamed: AVR.8, IC5.8, Q1.1
unnamed: AVR.7, IC5.7, Q1.3
unnamed: AVR1.8, IC1.8, Q2.1
unnamed: AVR1.7, IC1.7, Q2.3
unnamed: AVR2.8, IC2.8, Q3.1
unnamed: AVR2.7, IC2.7, Q3.3
unnamed: AVR3.8, IC3.8, Q4.1
unnamed: AVR3.7, IC3.7, Q4.3
RESET: AVR.29, IC5.29, JP5.P$1, JP25.P$1, R2.1
RESET1: AVR1.29, IC1.29, JP29.P$1, JP50.P$1, R1.1
RESET2: AVR2.29, IC2.29, JP54.P$1, JP75.P$1, R3.1
RESET3: AVR3.29, IC3.29, JP79.P$1, JP100.P$1, R4.1
RXI: AVR.30, IC5.30, JP2.P$1
RXI1: AVR1.30, IC1.30, JP27.P$1
RXI2: AVR2.30, IC2.30, JP52.P$1
RXI3: AVR3.30, IC3.30, JP77.P$1
SCK: AVR.17, IC5.17, NRF24.5
SCK1: AVR1.17, IC1.17, NRF1.5
SCK2: AVR2.17, IC2.17, NRF2.5
SCK3: AVR3.17, IC3.17, NRF3.5
TXO: AVR.31, IC5.31, JP4.P$1
TXO1: AVR1.31, IC1.31, JP28.P$1
TXO2: AVR2.31, IC2.31, JP53.P$1
TXO3: AVR3.31, IC3.31, JP78.P$1
VBAT: C2.1, JP6.P$1, JP24.P$1, LDO1.3
VBAT1: C8.1, JP30.P$1, JP49.P$1, LDO2.3
VBAT2: C14.1, JP55.P$1, JP74.P$1, LDO3.3
VBAT3: C19.1, JP80.P$1, JP99.P$1, LDO4.3

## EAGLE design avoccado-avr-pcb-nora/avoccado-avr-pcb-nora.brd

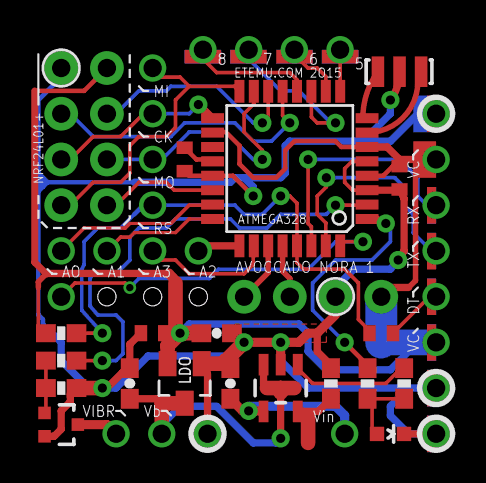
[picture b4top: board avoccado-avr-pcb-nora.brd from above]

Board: 2 copper layers, 51 parts (1 on the bottom side), 34 nets.

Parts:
AVR: ATMEGA328P; TQFP32-08
C1, C2, C3, C10: 0.1uF; C0402
C4, C5, C6: 4.7uF; 0603-CAP
D1: LED; LED-0603
JP2, JP4, JP5, JP27, JP28, JP29: M021X02_NO_SILK; 1X02_NO_SILK
JP3, JP6, JP8, JP9, JP10, JP11, JP12, JP13, JP14, JP15, JP17, JP18, JP19, JP20, JP21, JP22, JP23, JP24, JP25, JP26: M01NOSILK-KIT; 1X01NS-KIT
LDO: MCP1703CB; SOT23
LOGO1: OSHW-LOGOS; OSHW-LOGO-S
Q1: 16MHz; RESONATOR-SMD
Q2: FET; SOT323
R1, R4, R6: 1K; 0603-RES
R2: 10K; 0603-RES
R3: Rchg; 0603-RES
R5: 1M; 0603-RES
TP1, TP2, TP6, TP7, TP8: M01NOSILK-KIT; 1X01NS-KIT
U2: MCP73831; SOT23-5

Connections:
3.3V: AVR.4, AVR.6, AVR.18, C3.2, C6.1, C10.1, JP2.2, JP4.1, JP11.1, JP18.1, LDO.2, R2.2
5V: C4.1, JP17.1, U2.4
A0: AVR.23, JP19.1
A1: AVR.24, JP20.1
A2: AVR.25, JP21.1
A3: AVR.26, JP22.1
A4: AVR.27, JP5.2
A5: AVR.28, JP5.1
A7-NRF-IRQ: AVR.22, JP29.2
AREF: AVR.20, C1.2
CHG-PROG: R3.2, U2.5
D3: AVR.1, R6.1
D4: AVR.2, R1.1
D5: AVR.9, TP1.1
D6: AVR.10, TP6.1
D7: AVR.11, TP7.1
D8: AVR.12, TP8.1
D9: AVR.13, JP27.1
D10: AVR.14, JP27.2
DTR: C2.2, JP10.1
GND: AVR.3, AVR.5, AVR.21, C1.1, C3.1, C4.2, C5.2, C6.2, C10.2, D1.C, JP2.1, JP3.1, JP4.2, JP6.1, JP25.1, JP26.1, LDO.1, Q1.2, Q2.2, R3.1, R5.1, U2.2
LED: D1.A, R4.1, R6.2
MISO: AVR.16, JP12.1, JP29.1
MOSI: AVR.15, JP14.1, JP28.2
unnamed: AVR.8, Q1.1
unnamed: AVR.7, Q1.3
unnamed: Q2.1, R1.2, R5.2
RESET: AVR.29, C2.1, JP15.1, R2.1
RXI: AVR.30, JP8.1
SCK: AVR.17, JP13.1, JP28.1
SOC: R4.2, U2.1
TXO: AVR.31, JP9.1
VBAT: C5.1, JP24.1, LDO.3, U2.3
VIBR: JP23.1, Q2.3

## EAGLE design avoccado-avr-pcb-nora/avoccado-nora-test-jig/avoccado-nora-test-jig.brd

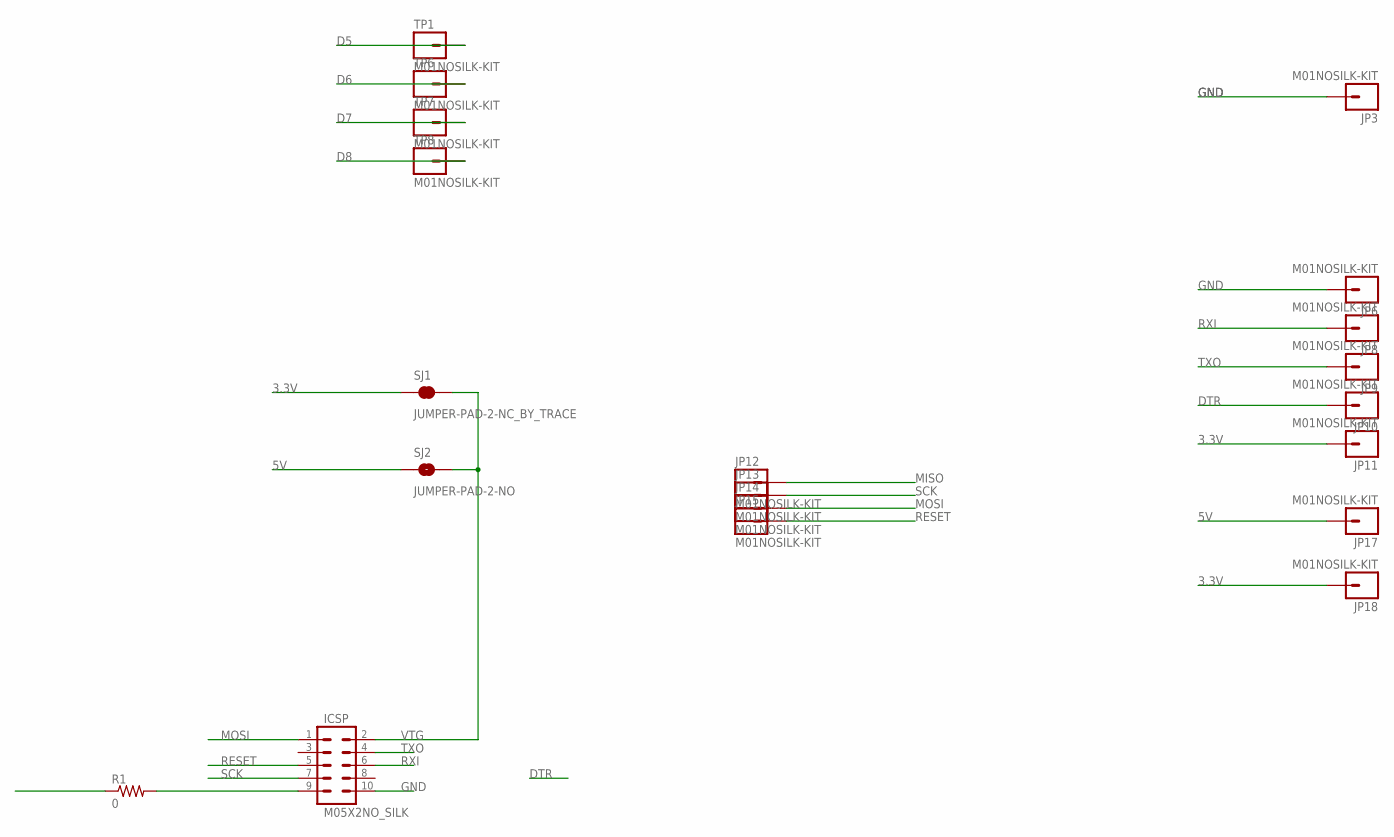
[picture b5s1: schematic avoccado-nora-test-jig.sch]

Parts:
ICSP: M05X2NO_SILK; 2X5_NOSILK
JP3, JP6, JP8, JP9, JP10, JP11, JP12, JP13, JP14, JP15, JP17, JP18: M01NOSILK-KIT; 1X01NS-KIT
R1: 0; 1206
SJ1: JUMPER-PAD-2-NC_BY_TRACE; PAD-JUMPER-2-NC_BY_TRACE_YES_SILK
SJ2: JUMPER-PAD-2-NO; PAD-JUMPER-2-NO_NO_SILK
TP1, TP6, TP7, TP8: M01NOSILK-KIT; 1X01NS-KIT

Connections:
3.3V: JP11.1, JP18.1, SJ1.1
5V: JP17.1, SJ2.1
D5: TP1.1
D6: TP6.1
D7: TP7.1
D8: TP8.1
DTR: JP10.1
GND: ICSP.10, JP3.1, JP6.1
MISO: JP12.1, R1.1
MISO1: ICSP.9, R1.2
MOSI: ICSP.1, JP14.1
RESET: ICSP.5, JP15.1
RXI: ICSP.6, JP8.1
SCK: ICSP.7, JP13.1
TXO: ICSP.4, JP9.1
VTG: ICSP.2, SJ1.2, SJ2.2

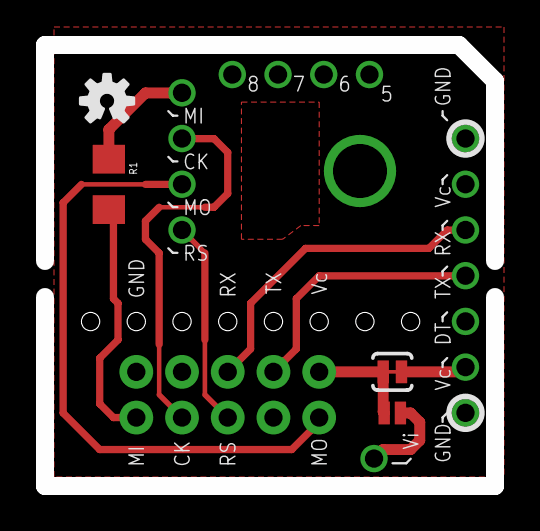
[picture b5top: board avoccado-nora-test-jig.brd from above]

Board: 2 copper layers, 25.0 x 24.5 mm, 21 parts (1 on the bottom side), 11 nets.

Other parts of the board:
LOGO2: OSHW-LOGOS; OSHW-LOGO-S

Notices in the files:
parts and their libraries:
SparkFun-DiscreteSemi: Licensing: Creative Commons ShareAlike 4.0 International - https://creativecommons.org/licenses/by-sa/4.0
